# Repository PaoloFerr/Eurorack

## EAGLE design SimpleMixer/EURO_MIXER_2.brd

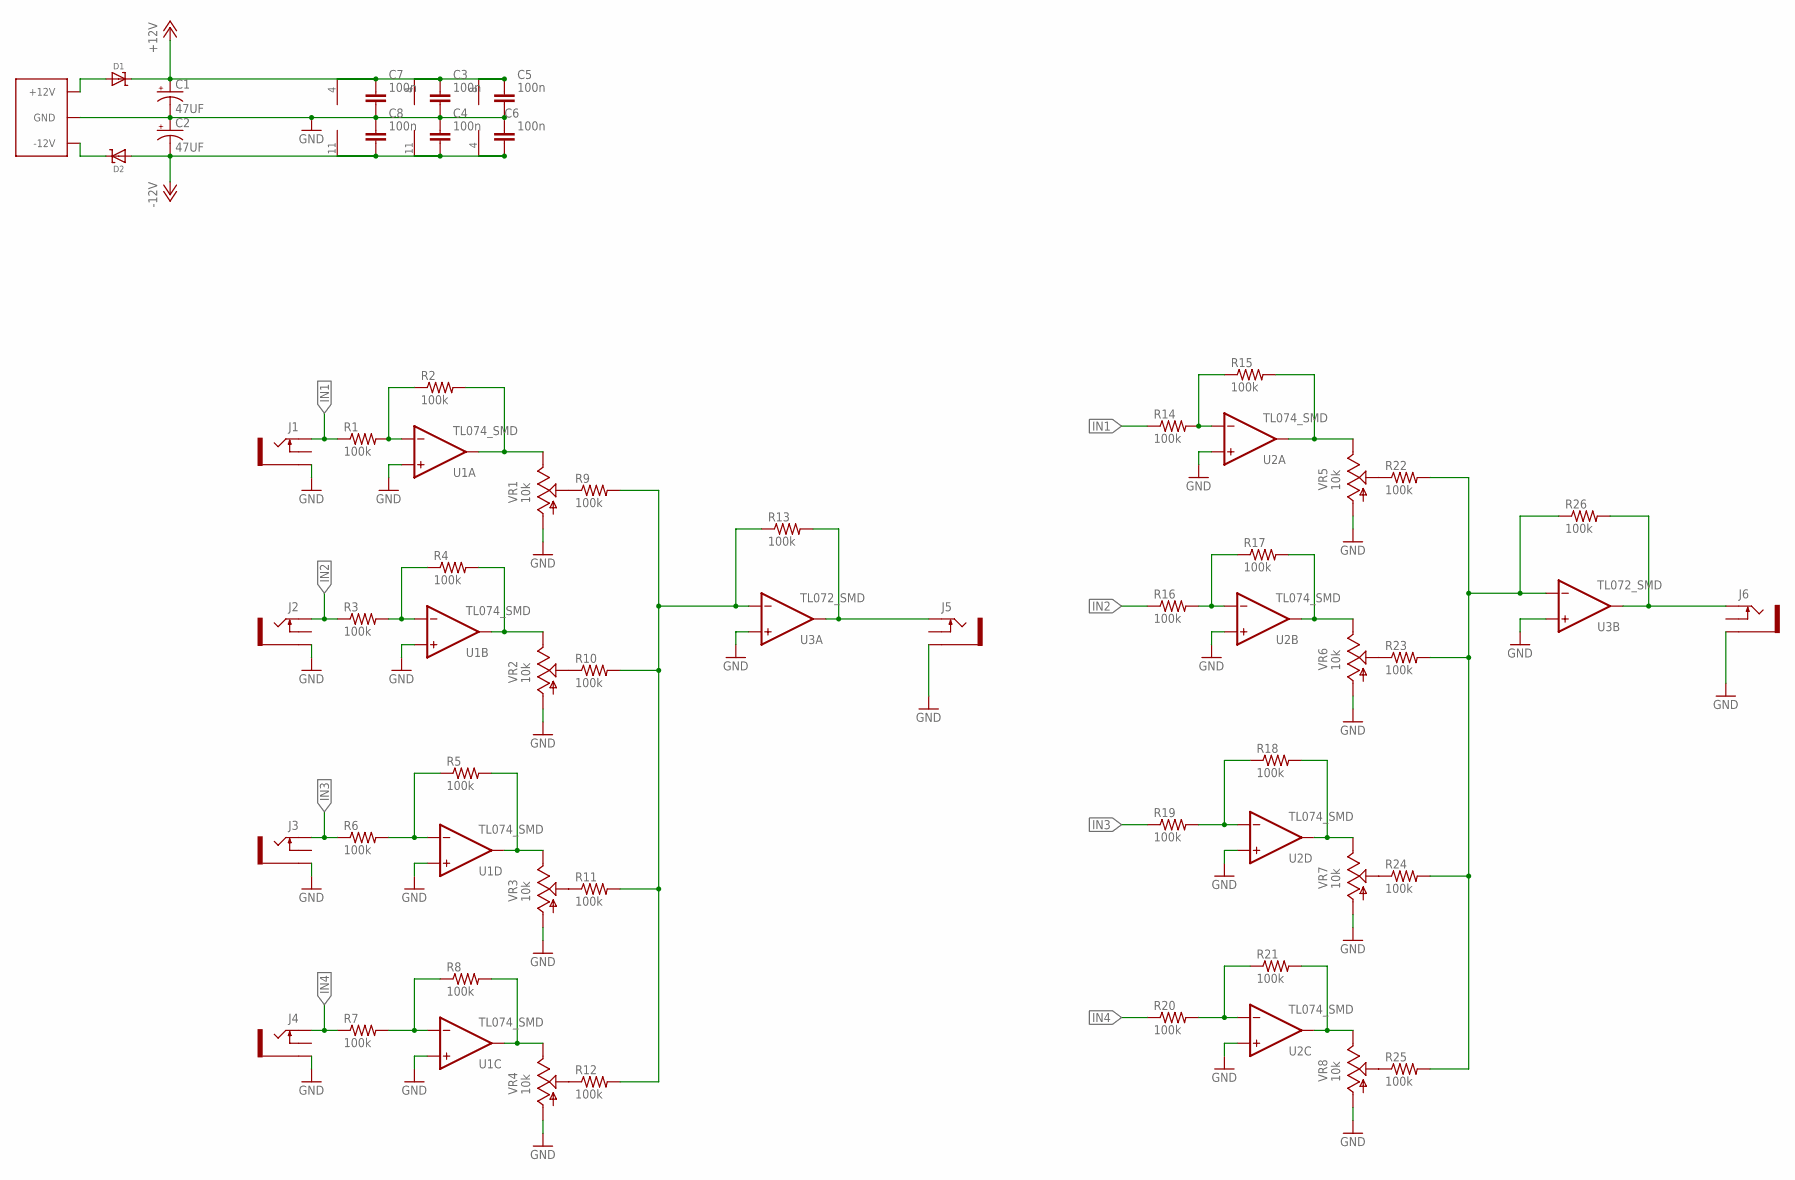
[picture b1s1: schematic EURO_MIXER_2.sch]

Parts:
C1, C2: 47UF; PANASONIC_D
C3, C4, C5, C6, C7, C8: 100n; CAPC2012X110
D1, D2: DIODE-SCHOTTKYSOD-123; SOD-123
J1, J2, J3, J4, J5, J6: THONKICONNNEW; WQP-PJ301M-12_JACK
JP1: EURO_POWER_LOCKSKINNY; EURO_POWER_HEADER
R1, R2, R3, R4, R5, R6, R7, R8, R9, R10, R11, R12, R13, R14, R15, R16, R17, R18, R19, R20, R21, R22, R23, R24, R25, R26: 100k; RESC2012X65
U1, U2: TL074_SMD; SO14
U3: TL072_SMD; SO08
VR1, VR2, VR3, VR4, VR5, VR6, VR7, VR8: 10k; 9MM_SNAP-IN_POT

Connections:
+12V: C1.+, C3.1, C5.1, C7.1, D1.C, U1.4 (V+), U2.4 (V+), U3.8 (V+)
-12V: C2.-, C4.2, C6.2, C8.2, D2.A, U1.11 (V-), U2.11 (V-), U3.4 (V-)
GND: C1.-, C2.+, C3.2, C4.1, C5.2, C6.1, C7.2, C8.1, J1.P$3_SLEEVE (SLEEVE), J2.P$3_SLEEVE (SLEEVE), J3.P$3_SLEEVE (SLEEVE), J4.P$3_SLEEVE (SLEEVE), J5.P$3_SLEEVE (SLEEVE), J6.P$3_SLEEVE (SLEEVE), JP1.3 (GND), JP1.4 (GND), JP1.5 (GND), JP1.6 (GND), JP1.7 (GND), JP1.8 (GND), U1.3 (+IN), U1.5 (+IN), U1.10 (+IN), U1.12 (+IN), U2.3 (+IN), U2.5 (+IN), U2.10 (+IN), U2.12 (+IN), U3.3 (+IN), U3.5 (+IN), VR1.1 (A), VR2.1 (A), VR3.1 (A), VR4.1 (A), VR5.1 (A), VR6.1 (A), VR7.1 (A), VR8.1 (A)
IN1: J1.P$1_TIP (TIP), R1.1, R14.1
IN2: J2.P$1_TIP (TIP), R3.1, R16.1
IN3: J3.P$1_TIP (TIP), R6.1, R19.1
IN4: J4.P$1_TIP (TIP), R7.1, R20.1
unnamed: J6.P$1_TIP (TIP), R26.2, U3.7 (OUT)
unnamed: R1.2, R2.1, U1.2 (-IN)
unnamed: R2.2, U1.1 (OUT), VR1.3 (E)
unnamed: D1.A, JP1.9 (+12V), JP1.10 (+12V)
unnamed: R7.2, R8.1, U1.9 (-IN)
unnamed: R4.2, U1.7 (OUT), VR2.3 (E)
unnamed: R3.2, R4.1, U1.6 (-IN)
unnamed: R5.2, U1.14 (OUT), VR3.3 (E)
unnamed: R14.2, R15.1, U2.2 (-IN)
unnamed: R9.1, VR1.2 (S)
unnamed: R8.2, U1.8 (OUT), VR4.3 (E)
unnamed: R10.1, VR2.2 (S)
unnamed: R11.1, VR3.2 (S)
unnamed: R12.1, VR4.2 (S)
unnamed: R9.2, R10.2, R11.2, R12.2, R13.1, U3.2 (-IN)
unnamed: R5.1, R6.2, U1.13 (-IN)
unnamed: J5.P$1_TIP (TIP), R13.2, U3.1 (OUT)
unnamed: R15.2, U2.1 (OUT), VR5.3 (E)
unnamed: R17.2, U2.7 (OUT), VR6.3 (E)
unnamed: R18.2, U2.14 (OUT), VR7.3 (E)
unnamed: R21.2, U2.8 (OUT), VR8.3 (E)
unnamed: R22.1, VR5.2 (S)
unnamed: R23.1, VR6.2 (S)
unnamed: R24.1, VR7.2 (S)
unnamed: R25.1, VR8.2 (S)
unnamed: R22.2, R23.2, R24.2, R25.2, R26.1, U3.6 (-IN)
unnamed: R18.1, R19.2, U2.13 (-IN)
unnamed: R16.2, R17.1, U2.6 (-IN)
unnamed: R20.2, R21.1, U2.9 (-IN)
unnamed: D2.C, JP1.1 (-12V), JP1.2 (-12V)

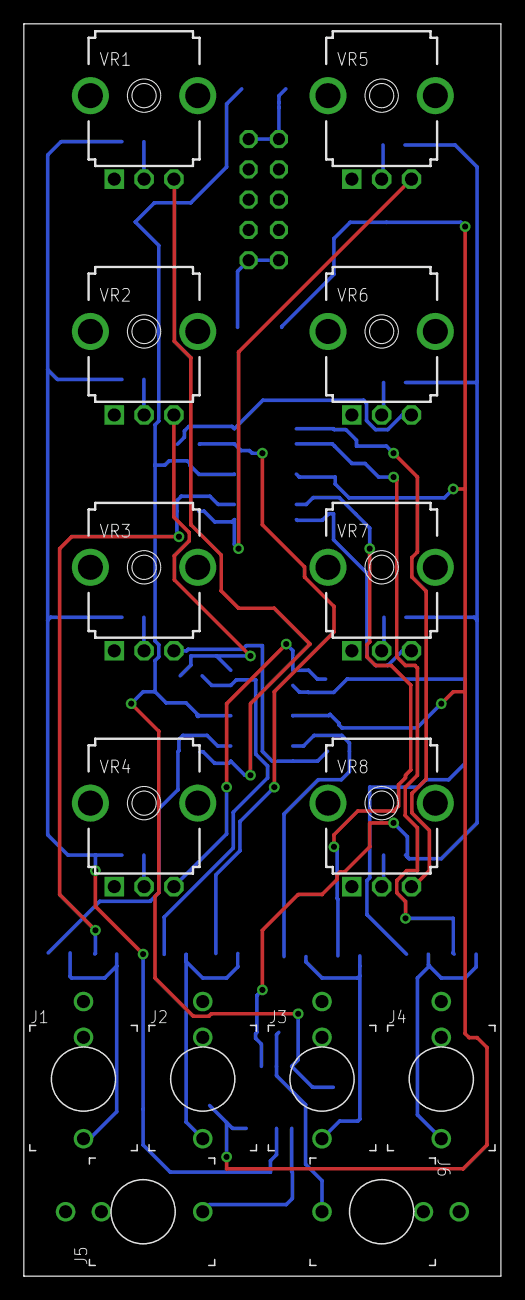
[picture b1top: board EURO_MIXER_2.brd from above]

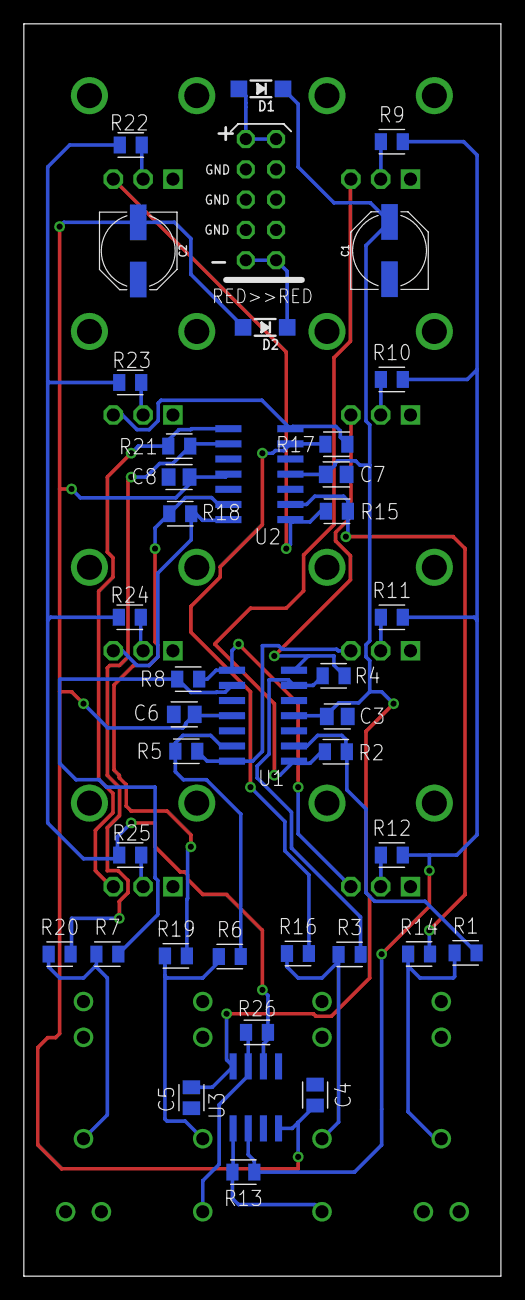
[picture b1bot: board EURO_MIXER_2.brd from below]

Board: 2 copper layers, 40.0 x 105.0 mm, 54 parts (40 on the bottom side), 37 nets.

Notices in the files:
parts and their libraries:
SparkFun-Capacitors: Licensing: Creative Commons ShareAlike 4.0 International - https://creativecommons.org/licenses/by-sa/4.0
